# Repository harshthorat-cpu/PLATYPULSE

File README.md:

# PLATYPULSE

### SRA Eklavya 2026 Project - Platypulse

> A unified handheld platform for RF, RFID/NFC, and IR wireless experimentation — built on the ESP32-S3.

## Problem Statement

Understanding and experimenting with different wireless communication technologies often requires multiple dedicated tools, modules, and software environments. RF, RFID/NFC, and IR each operate differently and use different communication methods, making it difficult to explore them together in a simple and accessible setup.

## Our Solution

*One board, three wireless worlds — RF, RFID/NFC, and IR, brought together.*

Platypulse is designed as a unified handheld platform that brings RF, RFID/NFC, and IR capabilities into a single embedded system. Built around the ESP32-S3, it provides dedicated hardware for interacting with different wireless technologies while offering a common interface for capturing, analyzing, storing, and transmitting supported signals. The goal is to make wireless experimentation more accessible by combining multiple capabilities into one compact platform for learning, prototyping, and development.

## Features

*Everything you need to capture, analyze, and replay wireless signals — in one device.*

- **RFID/NFC**: Read, write, and manage supported cards, tags, and stickers.
- **UID Support**: Modify the UID of compatible changeable-UID cards.
- **IR Remote**: Learn, store, and replay IR signals.
- **Sub-GHz RF**: Receive, store, analyze, and transmit supported RF signals.
- **Custom PCB**: Purpose-built PCB integrating the core communication modules.
- **Custom UI**: Unified interface for controlling and managing all major functions.

## Prerequisites

*What you'll need on the hardware and software side to build and run Platypulse.*

### Hardware

- ESP32-S3 development environment
- PN532 RFID/NFC module
- CC1101 Sub-GHz RF module
- IR Receiver & IR LED
- TFT Display

### Software

- **ESP-IDF** — firmware development for the ESP32-S3
- **GNU Radio / Software Defined Radio (SDR)** — RF signal testing and analysis
- **KiCad** — schematic design and PCB development
- **Onshape** — mechanical and enclosure design

## Media

*See Platypulse in action across NFC, RF, and IR.*

**Connecting to Wi-Fi via NFC** — demonstrates connecting to Wi-Fi directly using a single NFC sticker containing the required instructions, eliminating the need to manually enter the Wi-Fi password and enabling automated tasks.

https://github.com/user-attachments/assets/eea3f232-0957-4e07-8702-c358589d3c55

**Transmitting an RF Signal** — demonstrates the transmission of an RF signal through the CC1101 module.

https://github.com/user-attachments/assets/e0021282-87bb-4f81-9ff2-c89db1f22ec8

**Receiving an RF Signal** — demonstrates the process of receiving an RF signal through the CC1101 module.

https://github.com/user-attachments/assets/8b9e34c6-dc06-4a26-969a-4266ece2f23d

**Capturing & Emulating an IR Signal** — demonstrates capturing and emulating an IR signal, used here to change the AC temperature.

https://github.com/user-attachments/assets/e1bdd879-e367-4fc6-8ea2-27d7d49550e6

## Repository Structure 
```c
PLATYPULSE
├── Docs/
│   └── Platypulse_Report 
├── Firmware/
│   ├── CC1101/                             
│   │   ├── cc1101_ook_rx/
│   │   │                        
│   │   ├── gnu-radio-scripts/
│   │   └── register_test/
│   │       
│   │                            
│   ├── IR/                             
│   │   ├── Receiver/
│   │   │   └── receiver_test/
│   │   ├── ir_transmitter/
│   │   │                         
│   │   └── store_and_emulate/
│   │                        
│   ├── PN532/                               
│   │   └── testingcode/
│   │                         
│   └── UI/                                  
│       └── ui_control/
│           
│                             
├── PCB/
│   └── kicad/
│                               
│           
├── media/                                   
├── .gitignore
└── README.md
```
## Installing

*Get up and running with Platypulse in three simple steps.*

1. Cloning the repo

```c
git clone https://github.com/harshthorat-cpu/PLATYPULSE.git
```

2. Working on the particular folder

```c
cd PLATYPULSE
cd <folder name you want>
```

3. Running the code

```c
idf.py set-target esp32s3
idf.py build
idf.py flash
```

## Authors

- [Harsh Thorat](https://github.com/harshthorat-cpu)
- [Lucky Belel](https://github.com/belellucky-15)

## Acknowledgement

*With gratitude to the tools, community, and mentors who made this possible.*

- Thanks for the ESP-IDF, KiCad, GNU Radio, and Onshape for their excellent tools that helped us make our project.
- Thanks to our Robotics Club [SRA-VJTI](https://github.com/sra-vjti).
- Special thanks to our mentors [Pushkar Dube](https://github.com/pushkardube), [Lakshya Lalwani](https://github.com/Lakshyaa1), and [Sarvaarth Narang](https://github.com/SarvaarthN).

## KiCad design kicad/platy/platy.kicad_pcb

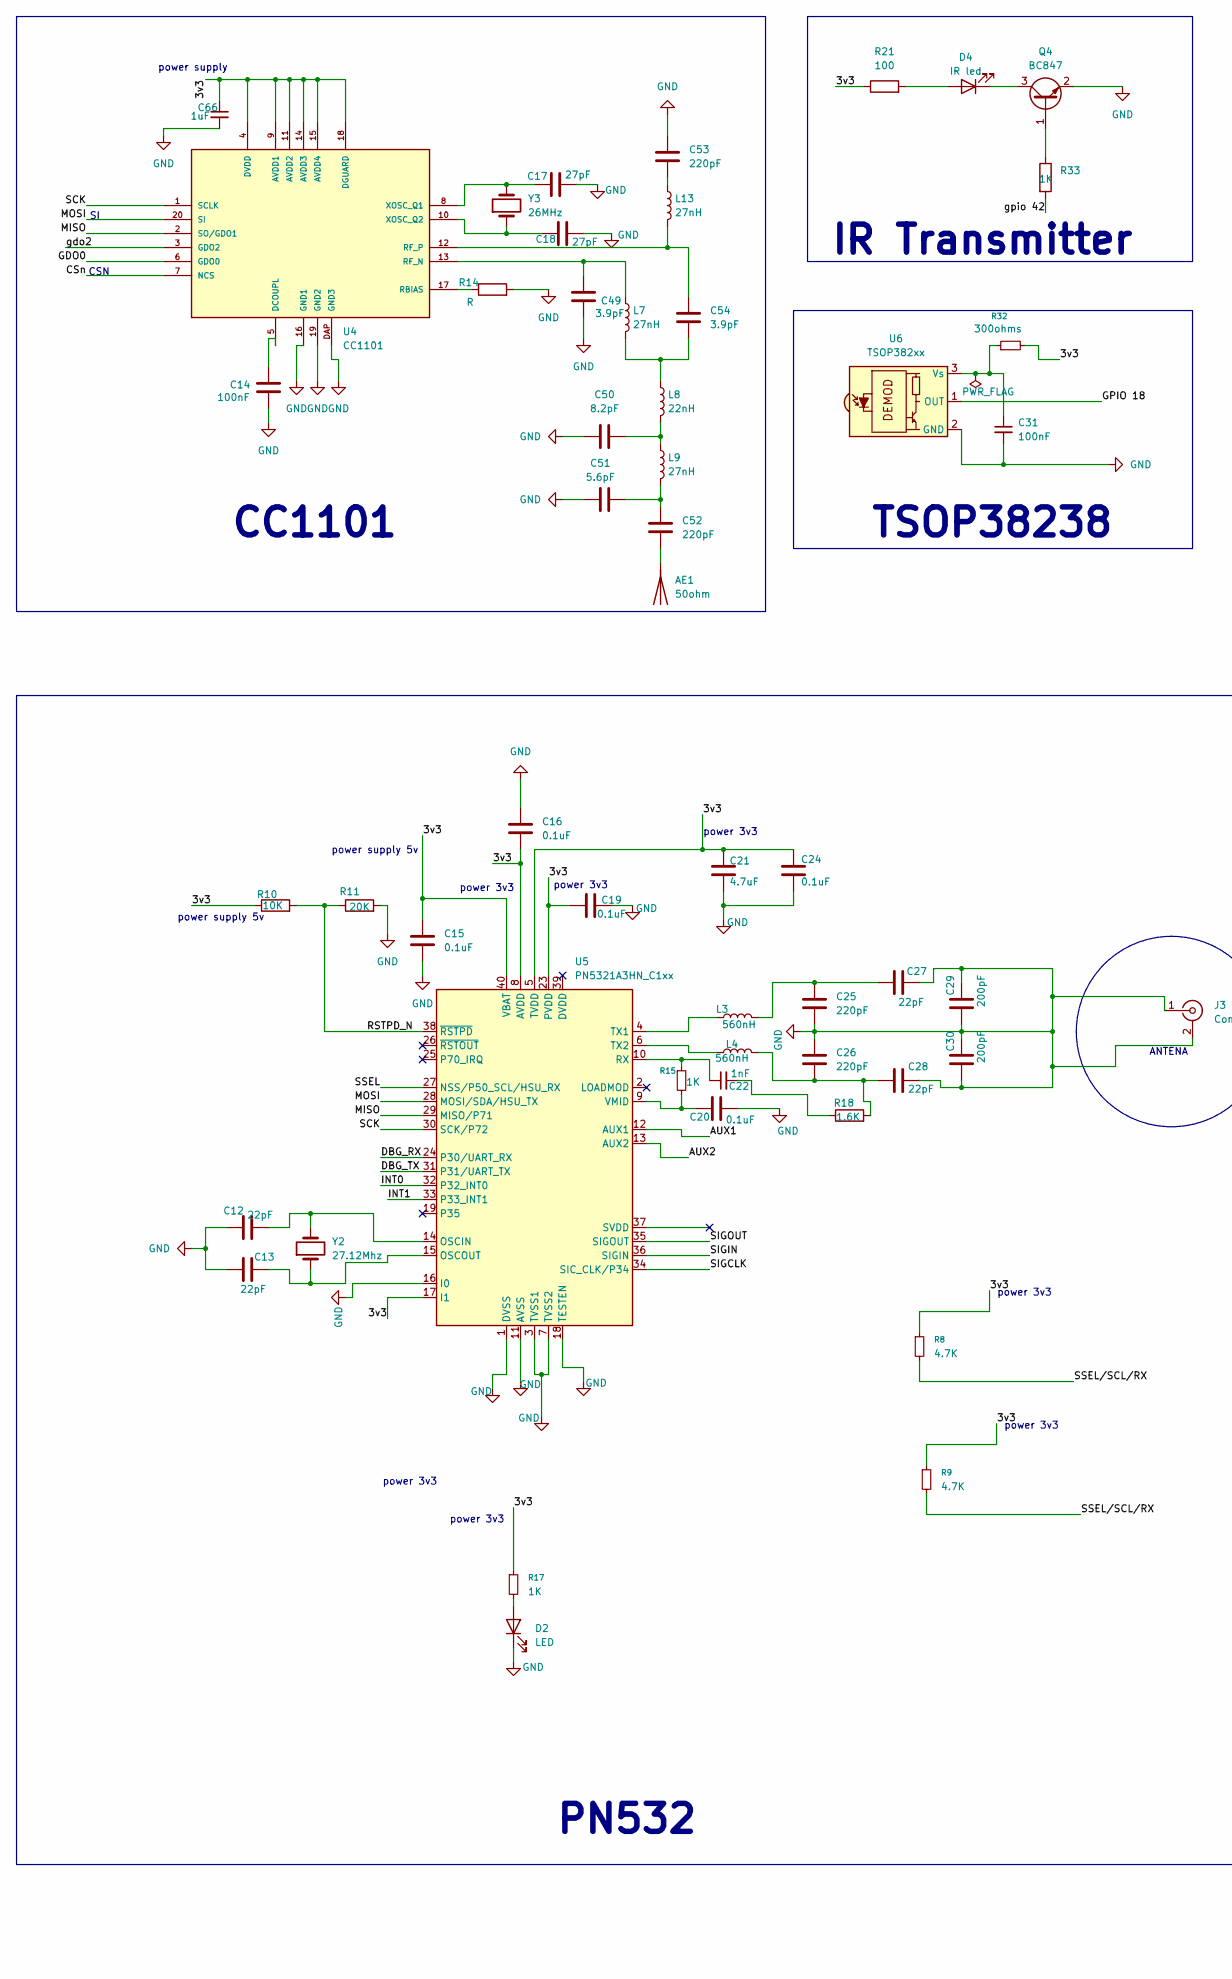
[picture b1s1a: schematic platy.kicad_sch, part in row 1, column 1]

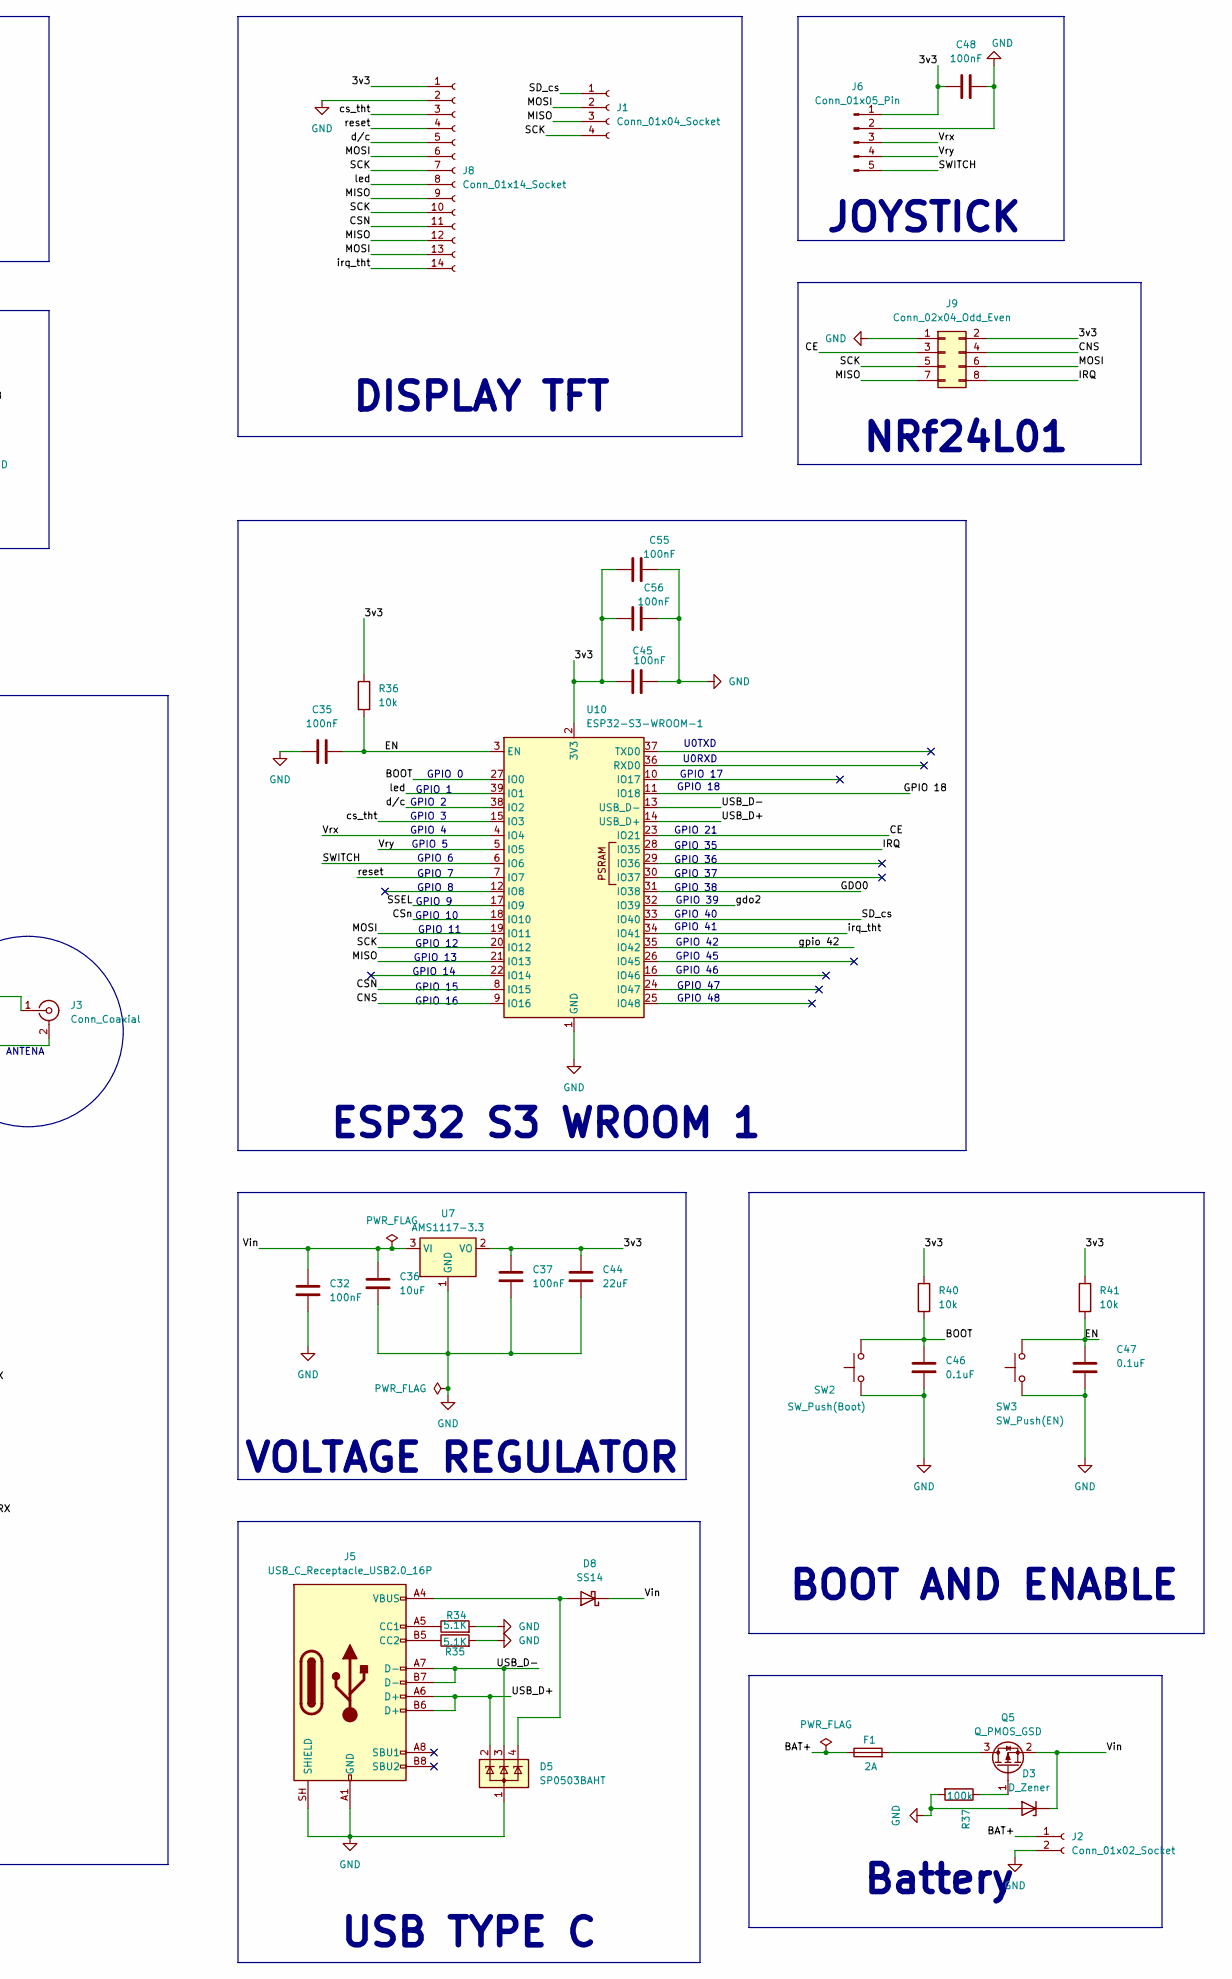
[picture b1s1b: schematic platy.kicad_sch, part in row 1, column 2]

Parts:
AE1: 50ohm; SMA_Amphenol_132134_Vertical
C12, C13, C27, C28: 22pF; C_0805_2012Metric
C14, C31, C32, C35, C37, C45, C48, C55, C56: 100nF; C_0805_2012Metric
C15, C16, C19, C20, C24, C46, C47: 0.1uF; C_0805_2012Metric
C17, C18: 27pF; C_0805_2012Metric
C21: 4.7uF; C_0805_2012Metric
C22: 1nF; C_0805_2012Metric
C25, C26, C52, C53: 220pF; C_0805_2012Metric
C29, C30: 200pF; C_0805_2012Metric
C36: 10uF; C_0805_2012Metric
C44: 22uF; C_0805_2012Metric
C49, C54: 3.9pF; C_0805_2012Metric
C50: 8.2pF; C_0805_2012Metric
C51: 5.6pF; C_0805_2012Metric
C66: 1uF; C_0805_2012Metric
D2: LED; LED_0805_2012Metric
D3: D_Zener; D_0805_2012Metric
D4: IR led; LED_D3.0mm
D5: SP0503BAHT; SOT-143
D8: SS14; D_SMA
F1: 2A; Fuse_0805_2012Metric
J1: Conn_01x04_Socket; PinSocket_1x04_P2.54mm_Vertical
J2: Conn_01x02_Socket; JST_EH_S2B-EH_1x02_P2.50mm_Horizontal
J3: Conn_Coaxial; U.FL_Molex_MCRF_73412-0110_Vertical
J5: USB_C_Receptacle_USB2.0_16P; USB_C_Receptacle_GCT_USB4105-xx-A_16P_TopMnt_Horizontal
J6: Conn_01x05_Pin; PinHeader_1x05_P2.54mm_Vertical
J8: Conn_01x14_Socket; PinSocket_1x14_P2.54mm_Vertical
J9: Conn_02x04_Odd_Even; PinSocket_2x04_P2.54mm_Vertical
L3, L4: 560nH; L_0805_2012Metric
L7, L9, L13: 27nH; L_0805_2012Metric
L8: 22nH; L_0805_2012Metric
Q4: BC847; SOT-23
Q5: Q_PMOS_GSD; TSOT-23
R8, R9: 4.7K; R_0805_2012Metric
R10: 10K; R_0805_2012Metric
R11: 20K; R_0805_2012Metric
R14: R; R_0805_2012Metric
R15, R17, R33: 1K; R_0805_2012Metric
R18: 1.6K; R_0805_2012Metric
R21: 100; R_0805_2012Metric
R32: 300ohms; R_0805_2012Metric
R34, R35: 5.1K; R_0805_2012Metric
R36, R40, R41: 10k; R_0805_2012Metric
R37: 100k; R_0805_2012Metric
SW2: SW_Push(Boot); SW_PUSH_6mm
SW3: SW_Push(EN); SW_PUSH_6mm
U4: CC1101; QLP20
U5: PN5321A3HN_C1xx; HVQFN-40-1EP_6x6mm_P0.5mm_EP4.1x4.1mm
U6: TSOP382xx; Vishay_MINICAST-3Pin
U7: AMS1117-3.3; SOT-223-3_TabPin2
U10: ESP32-S3-WROOM-1
Y2: 27.12Mhz; Crystal_SMD_5032-2Pin_5.0x3.2mm
Y3: 26MHz; Crystal_SMD_5032-2Pin_5.0x3.2mm

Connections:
/3v3: C15.1, C16.2, C19.1, C21.1, C24.1, C37.1, C44.1, C45.1, C48.1, C55.1, C56.1, C66.1, J6.1, J8.1, J9.2, R8.1, R9.1, R10.1, R17.1, R21.1, R32.2, R36.1, R40.1, R41.1, U4.4 (DVDD), U4.9 (AVDD1), U4.11 (AVDD2), U4.14 (AVDD3), U4.15 (AVDD4), U4.18 (DGUARD), U5.5 (TVDD), U5.8 (AVDD), U5.17 (I1), U5.23 (PVDD), U5.40 (VBAT), U7.2 (VO), U10.2 (3V3)
/AUX1: U5.12 (AUX1)
/AUX2: U5.13 (AUX2)
/BAT+: F1.1, J2.1
/BOOT: C46.1, R40.2, SW2.2, U10.27 (IO0)
/CE: J9.3, U10.23 (IO21)
/CNS: J9.4, U10.9 (IO16)
/CSN: J8.11, U10.8 (IO15)
/CSn: U4.7 (NCS), U10.18 (IO10)
/DBG_RX: U5.24 (P30/UART_RX)
/DBG_TX: U5.31 (P31/UART_TX)
/EN: C35.1, C47.1, R36.2, R41.2, SW3.2, U10.3 (EN)
/GDO0: U4.6 (GDO0), U10.31 (IO38)
/GPIO 18: U6.1 (OUT), U10.11 (IO18)
/INT0: U5.32 (P32_INT0)
/INT1: U5.33 (P33_INT1)
/IRQ: J9.8, U10.28 (IO35)
/MISO: J1.3, J8.9, J8.12, J9.7, U4.2 (SO/GDO1), U5.29 (MISO/P71), U10.21 (IO13)
/MOSI: J1.2, J8.6, J8.13, J9.6, U4.20 (SI), U5.28 (MOSI/SDA/HSU_TX), U10.19 (IO11)
/RSTPD_N: R10.2, R11.1, U5.38 (~RSTPD)
/SCK: J1.4, J8.7, J8.10, J9.5, U4.1 (SCLK), U5.30 (SCK/P72), U10.20 (IO12)
/SD_cs: J1.1, U10.33 (IO40)
/SIGCLK: U5.34 (SIC_CLK/P34)
/SIGIN: U5.36 (SIGIN)
/SIGOUT: U5.35 (SIGOUT)
/SSEL: U5.27 (NSS/P50_SCL/HSU_RX), U10.17 (IO9)
/SWITCH: J6.5, U10.6 (IO6)
/USB_D+: D5.2 (K), J5.A6 (D+), J5.B6 (D+), U10.14 (USB_D+)
/USB_D-: D5.3 (K), J5.A7 (D-), J5.B7 (D-), U10.13 (USB_D-)
/Vin: C32.2, C36.1, D3.1 (K), D8.1 (K), Q5.2 (S), U7.3 (VI)
/Vrx: J6.3, U10.4 (IO4)
/Vry: J6.4, U10.5 (IO5)
/cs_tht: J8.3, U10.15 (IO3)
/d/c: J8.5, U10.38 (IO2)
/gdo2: U4.3 (GDO2), U10.32 (IO39)
/gpio 42: R33.2, U10.35 (IO42)
/irq_tht: J8.14, U10.34 (IO41)
/led: J8.8, U10.39 (IO1)
/reset: J8.4, U10.7 (IO7)
unnamed: AE1.1 (A_1), C52.1
unnamed 40: C25.1, C27.1, L3.2; also elsewhere on the board
unnamed 41: C26.2, C28.1, L4.2, R18.2; also elsewhere on the board
unnamed: C22.2, R18.1
unnamed: C50.1, L8.2, L9.1
unnamed: C51.1, C52.2, L9.2
unnamed: C53.1, L13.1
unnamed: C54.1, L7.2, L8.1
unnamed: D2.2 (A), R17.2
unnamed: D4.2 (A), R21.2
unnamed: D4.1 (K), Q4.3 (C)
unnamed: D5.4 (K), D8.2 (A), J5.A4 (VBUS), J5.A9 (VBUS), J5.B4 (VBUS), J5.B9 (VBUS)
unnamed: J5.A5 (CC1), R34.1
unnamed: J5.B5 (CC2), R35.1
unnamed: Q4.1 (B), R33.1
unnamed: F1.2, Q5.3 (D)
unnamed: R8.2, R9.2
unnamed: C14.1, U4.5 (DCOUPL)
unnamed: R14.1, U4.17 (RBIAS)
unnamed: C49.2, L7.1, U4.13 (RF_N)
unnamed: C54.2, L13.2, U4.12 (RF_P)
unnamed: C17.1, U4.8 (XOSC_Q1), Y3.2
unnamed: C18.1, U4.10 (XOSC_Q2), Y3.1
unnamed: C12.1, U5.14 (OSCIN), Y2.2
unnamed: C13.2, U5.15 (OSCOUT), Y2.1
unnamed: C22.1, R15.1, U5.10 (RX)
unnamed: L3.1, U5.4 (TX1)
unnamed: L4.1, U5.6 (TX2)
unnamed: C20.1, R15.2, U5.9 (VMID)
unnamed: C31.1, R32.1, U6.3 (Vs)

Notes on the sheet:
GPIO 3
GPIO 45
GPIO 36
power 3v3
GPIO 38
GPIO 13
GPIO 46
GPIO 47
GPIO 48
GPIO 0
GPIO 4
U0TXD
power supply
PN532
GPIO 9
GPIO 17
GPIO 18
BOOT AND ENABLE
GPIO 37
U0RXD
GPIO 14
GPIO 2
JOYSTICK
TSOP38238
GPIO 1
GPIO 42
GPIO 8
CC1101
GPIO 12
GPIO 11
CSN
power supply 5v
DISPLAY TFT
ANTENA
IR Transmitter
GPIO 35
GPIO 40
Battery
GPIO 6
ESP32 S3 WROOM 1

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
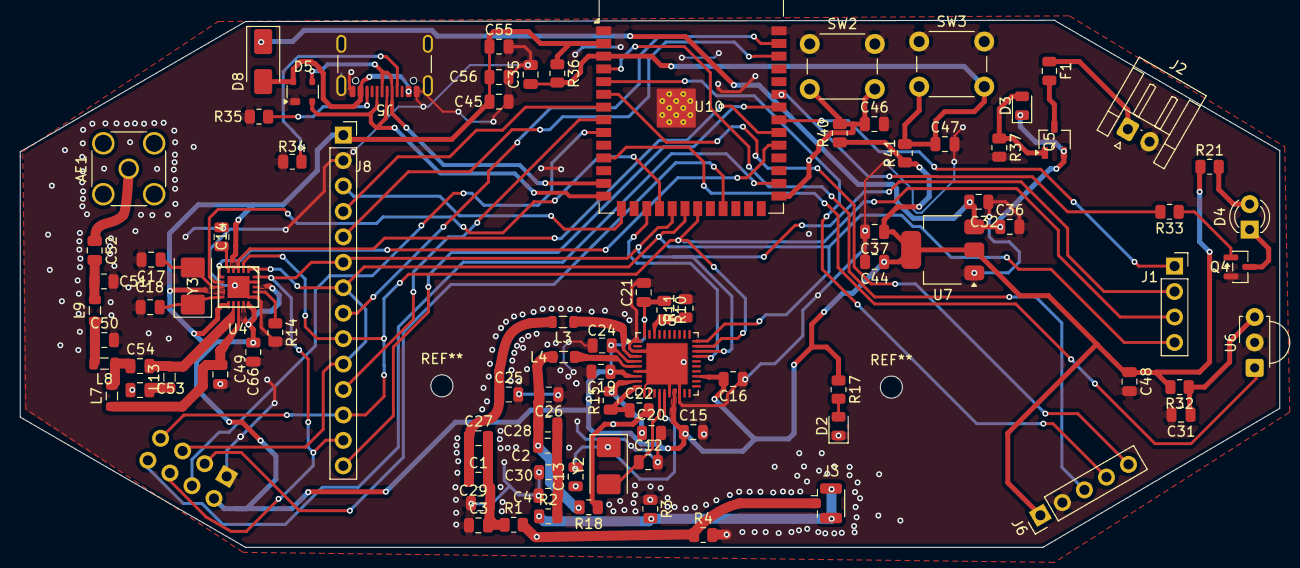
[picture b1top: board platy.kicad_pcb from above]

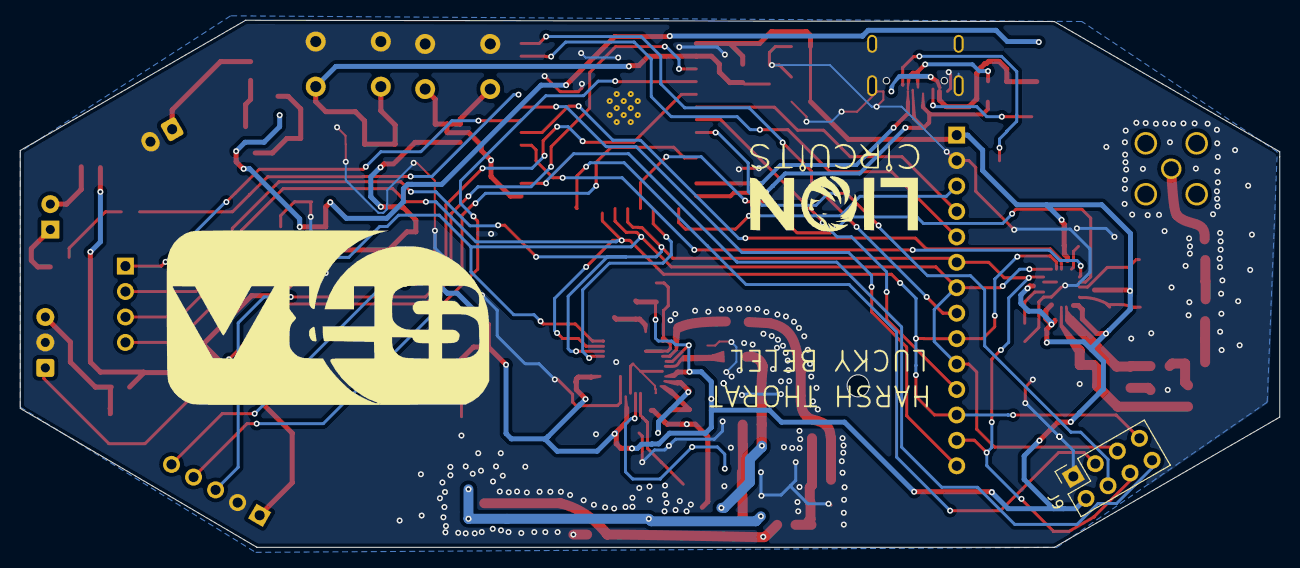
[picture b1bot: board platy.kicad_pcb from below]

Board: 2 copper layers, 125.8 x 52.6 mm, 92 parts (2 on the bottom side), 65 nets.

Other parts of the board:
C1, C2, C3, C4: NC; C_0805_2012Metric
R1, R2: 1.5; R_0805_2012Metric
R3, R4: NC; R_0805_2012Metric
lionckt: LOGO

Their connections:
unnamed 40: C1.1; also elsewhere on the board
unnamed 41: C2.1; also elsewhere on the board

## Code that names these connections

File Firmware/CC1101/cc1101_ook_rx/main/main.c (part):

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 *   SCK          GPIO18         SPI clock
 *   MOSI         GPIO23         SPI MOSI
 *   GDO1         GPIO19         Doubles as MISO/SO in SPI mode
 *   CSN          GPIO5          Chip select
 *   GDO0         GPIO4          Packet-received interrupt line
 *   GDO2         (not used)     Leave unconnected or wire to a spare GPIO
 *
 * Behavior:
 *  - Configures the CC1101 for ASK/OOK modulation at 433.92 MHz, 2400 baud,
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#define PIN_SCK   18
#define PIN_MOSI  23
#define PIN_MISO  19   /* physically wired to CC1101 GDO1 */
#define PIN_CSN   5
#define PIN_GDO0  4    /* packet-received interrupt */

#define SPI_HOST_USED SPI2_HOST

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
static inline void cc1101_cs_select(void)
{
    gpio_set_level(PIN_CSN, 0);
    /* CC1101 requirement: after CSN goes low, wait until SO (MISO/GDO1)
     * goes low, which signals the crystal oscillator is stable and the
     * chip is ready to accept the SPI header byte. */
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
static inline void cc1101_cs_deselect(void)
{
    gpio_set_level(PIN_CSN, 1);
}

static uint8_t cc1101_strobe(uint8_t cmd)
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
static void cc1101_reset(void)
{
    gpio_set_level(PIN_CSN, 1);
    esp_rom_delay_us(5);
    gpio_set_level(PIN_CSN, 0);
    esp_rom_delay_us(10);
    gpio_set_level(PIN_CSN, 1);
    esp_rom_delay_us(41);
    cc1101_strobe(CC1101_SRES);
    vTaskDelay(pdMS_TO_TICKS(10));
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    ESP_ERROR_CHECK(spi_bus_add_device(SPI_HOST_USED, &devcfg, &spi));

    gpio_config_t csn_conf = {
        .pin_bit_mask = (1ULL << PIN_CSN),
        .mode = GPIO_MODE_OUTPUT,
    };
    gpio_config(&csn_conf);
    gpio_set_level(PIN_CSN, 1);
}

static void gdo0_init(void)
{
    gpio_config_t io_conf = {
        .pin_bit_mask = (1ULL << PIN_GDO0),
        .mode = GPIO_MODE_INPUT,
        .pull_up_en = GPIO_PULLUP_DISABLE,
        .pull_down_en = GPIO_PULLDOWN_DISABLE,
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
    gdo0_evt_queue = xQueueCreate(10, sizeof(uint32_t));
    gpio_install_isr_service(0);
    gpio_isr_handler_add(PIN_GDO0, gdo0_isr_handler, (void *)PIN_GDO0);
}

void app_main(void)
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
